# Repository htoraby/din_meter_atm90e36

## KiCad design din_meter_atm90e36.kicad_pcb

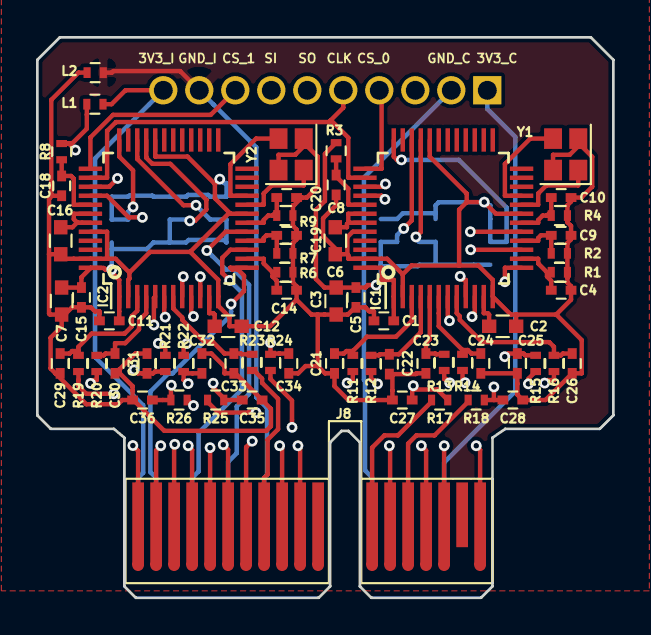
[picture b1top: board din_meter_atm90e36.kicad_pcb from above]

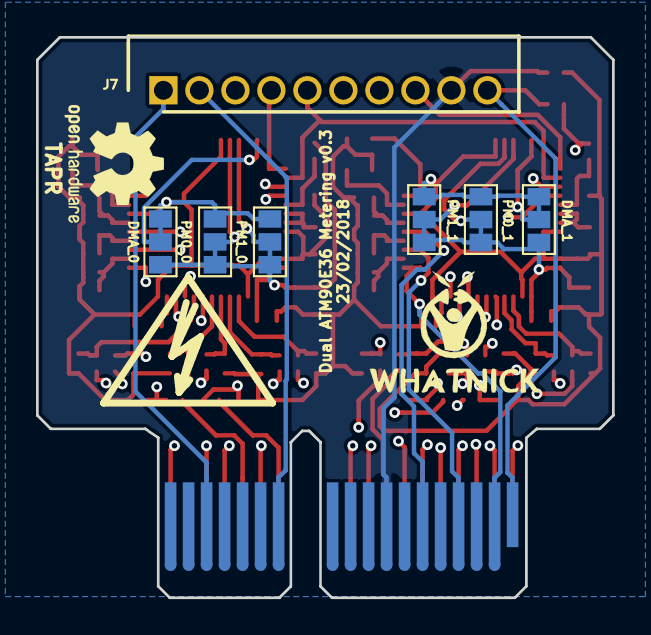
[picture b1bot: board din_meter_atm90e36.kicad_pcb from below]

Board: 4 copper layers, 32.0 x 31.1 mm, 75 parts (10 on the bottom side), 62 nets.

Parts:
C1, C5, C8, C11, C15, C18: 100n; C_0402
C2, C3, C6, C7, C12, C16: 10u; C_0603
C4, C9, C10, C14, C19, C20, C21, C22, C23, C24, C25, C26, C27, C28, C29, C30, C31, C32, C33, C34, C35, C36: 18n; C_0402
DMA_0, DMA_1: GS3
G1: LOGO; Whatnick_logo
G2: Logo_Open_Hardware_Small; OSHW-Logo2_7.3x6mm_SilkScreen
IC1, IC2: ATM90E36_ATM90E36; TQFP-48_7x7mm_Pitch0.5mm
J7: Conn_01x10; SHDR10W60P200_1X10_2150X400X335P
J8: Conn_02x18_Row_Letter_First; PCI-EXPRESS
L1, L2: L_Small; L_0402
PM0_0, PM0_1, PM1_0, PM1_1: GS3
R1, R2, R4, R6, R7, R9, R11, R12, R13, R14, R15, R16, R17, R18, R19, R20, R21, R22, R23, R24, R25, R26: 1K; R_0402
R3, R8: 10K; R_0402
SYM1: SYM_Flash_Small; Fsilk_HV
Y1, Y2: Crystal_GND24; Crystal_SMD_2520-4pin_2.5x2.0mm

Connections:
3V3_CPU: J7.1, J8.a16
3V3_ISO: J7.10, J8.a1, L1.2
+3V3: C1.2, C3.2, C5.2, C7.2, C11.2, C15.2, DMA_0.3, DMA_1.3, IC1.1, IC1.33, IC1.34, IC1.48, IC2.1, IC2.33, IC2.34, IC2.48, L1.1, PM0_0.2, PM0_0.3, PM0_1.2, PM0_1.3, PM1_0.2, PM1_0.3, PM1_1.2, PM1_1.3, R3.1, R8.1
CS_0: IC1.37, J7.4
CS_1: IC2.37, J7.8
DMA_0: C1.1, C2.1, C3.1, C4.1, C5.1, C6.2, C7.1, C8.2, C9.1, C10.1, C11.1, C12.1, C14.1, C15.1, C16.2, C18.2, C19.1, C20.1, C21.2, C22.2, C23.2, C24.2, C25.2, C26.2, C27.2, C28.2, C29.2, C30.2, C31.2, C32.2, C33.2, C34.2, C35.2, C36.2, DMA_0.1, DMA_0.2, DMA_1.1, DMA_1.2, IC1.2, IC1.12, IC1.19, IC1.32, IC1.36, IC1.44, IC1.47, IC2.2, IC2.12, IC2.19, IC2.32, IC2.36, IC2.44, IC2.47, L2.1, PM0_0.1, PM0_1.1, PM1_0.1, PM1_1.1, R1.2, R2.2, R4.2, R6.2, R7.2, R9.2, Y1.2, Y1.4, Y2.2, Y2.4
GND_CPU: J7.2, J8.a12
GND_ISO: J7.9, J8.a8, L2.2
I1N_0: C22.1, IC1.4, R12.1
I1N_1: C30.1, IC2.4, R20.1
I1P_0: C21.1, IC1.3, R11.1
I1P_1: C29.1, IC2.3, R19.1
I2N_0: C24.1, IC1.6, R14.1
I2N_1: C32.1, IC2.6, R22.1
I2P_0: C23.1, IC1.5, R13.1
I2P_1: C31.1, IC2.5, R21.1
I3N_0: C26.1, IC1.8, R16.1
I3N_1: C34.1, IC2.8, R24.1
I3P_0: C25.1, IC1.7, R15.1
I3P_1: C33.1, IC2.7, R23.1
IA1+: J8.b2, R11.2
IA1-: J8.b1, R12.2
IA2+: J8.b10, R19.2
IA2-: J8.b9, R20.2
IB1+: J8.b4, R13.2
IB1-: J8.b3, R14.2
IB2+: J8.b13, R21.2
IB2-: J8.b15, R22.2
IC1+: J8.b6, R15.2
IC1-: J8.b5, R16.2
IC2+: J8.b8, R23.2
IC2-: J8.b7, R24.2
IN1+: J8.b12, R17.2
IN1-: J8.b14, R18.2
IN2+: J8.b16, R25.2
IN2-: J8.b18, R26.2
IN_0: C28.1, IC1.10, R18.1
IN_1: C36.1, IC2.10, R26.1
IP_0: C27.1, IC1.9, R17.1
IP_1: C35.1, IC2.9, R25.1
MISO: IC1.39, IC2.39, J7.6
MOSI: IC1.40, IC2.40, J7.7
unnamed: C2.2, IC1.11
unnamed: C4.2, IC1.14, R1.1
unnamed: C6.1, IC1.42, IC1.43
unnamed: C8.1, IC1.41, R3.2
unnamed: C9.2, IC1.16, R2.1
unnamed: C10.2, IC1.18, R4.1
unnamed: C12.2, IC2.11
unnamed: C14.2, IC2.14, R6.1
unnamed: C16.1, IC2.42, IC2.43
unnamed: C18.1, IC2.41, R8.2
unnamed: C19.2, IC2.16, R7.1
unnamed: C20.2, IC2.18, R9.1
unnamed: IC1.20, Y1.1
unnamed: IC1.21, Y1.3
unnamed: IC2.20, Y2.1
unnamed: IC2.21, Y2.3
SCLK: IC1.38, IC2.38, J7.5
V1P: IC1.13, IC2.13, J8.a2
V2P: IC1.15, IC2.15, J8.a4
V3P: IC1.17, IC2.17, J8.a6

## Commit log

2017-12-11 Initial import
2017-12-11 Make passives smaller
2017-12-11 Added Hierarchial sheet
2017-12-25 Create sub-sheets and start layout
2018-01-01 Add some connector labels
2018-01-01 Wired up current samplers
2018-01-01 Add part values
2018-01-02 Change PCI-X pad names to lower case to match schema
2018-01-02 Change copper fill to GND
2018-01-02 Clean up part placement, prep for final place and route
2018-01-09 Intial work from Joslyn
2018-01-16 Try 4-layer
2018-01-16 Autoroute with 4-layer
2018-01-16 Upgrade to symbol library table format
2018-01-16 Hard wire pads
2018-01-19 Add meter gerbers
2018-01-19 Add new gerbers
2018-01-19 New gerber zip
2018-02-10 Fixed some silk, add ground plane and HTML BOM
2018-02-10 Fixed 1k reset resistor to 10k
2018-02-20 Added silkscreen dot to place chip
2018-02-22 Add some manf#
2018-02-22 Add manufacturer number and more details on silk
2018-02-23 Added step file and proper soldermask to open PCI-E connector
2018-02-23 New gerbers
2018-02-24 New BOM output
2018-03-02 rescue symbols
2018-03-02 Fix a trace outside board edge
2019-04-19 Change 3D models reference
